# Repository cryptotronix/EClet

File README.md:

EClet
=====

Driver for the Cryptotronix EClet containing an Atmel ATECC108

Status
---

This software is in ***BETA***. I have tested the below commands, but some there are some features and documentation that I would like to finish. If you use this software, it will configure your ECC108 in a non-reversible way. It will allow you to sign and verify with P256 keys but future features may be incompatible.

Releases
-----

You can download the latest release [here](https://github.com/cryptotronix/EClet/releases/download/0.1.1/eclet-0.1.1.tar.gz). You will also need [this](https://github.com/cryptotronix/libcrypti2c/releases/download/v0.2/libcryptoauth-0.2.tar.gz) release of libcryptoauth.

Building
----

Install build-essential, autotools-dev, automake, autoconf, libtool, libxml2-dev, check, texinfo, and libgcrypt (libgcrypt11-dev on Debian variants)

Run `./autogen.sh`. This will generate the required README file from README.md as well as installing the required ***BETA*** version of [libcryptoauth-0.2](https://github.com/cryptotronix/libcrypti2c) (`sudo` is used to install this library)

You can run `eclet` locally, or install it to the system by running `sudo make install`

Hardware
---

The Hardware folder has an example board layout. This software will also work on the [CryptoCape](https://www.sparkfun.com/products/12773).

Running
---

see `./eclet --help` for full details.  The default I2C bus is
`/dev/i2c-1` and this can be changed with the `-b` option.

Kernel option
---

If you build
[libcryptoauth](https://github.com/cryptotronix/libcrypti2c) with the
`-DUSE_KERNEL` flag and install the kernel module, this utility will
use that module if you pass in: `-b /dev/atsha0`.

Root
---

You'll need to run as root to access `/dev/i2c*` initially.  You can change this by adding your user to the `i2c` group with:

`sudo usermod -aG i2c user`

Or:

`sudo chmod o+rw /dev/i2c*`

Currently supported commands:

### state
```bash
eclet state
Factory
```

This is the first command you should run and verify it's in the Factory state.  This provides the assurance that the device has not been tampered during transit.

### personalize
```bash
eclet personalize
```

This is the second command you should run.  On success it will not output anything. It configures all slots (0-16) to be holders for P-256 ECC private keys, except slot 8, which is reserved for future use. Keys are not generated at this time. Each key must be individually generated with the `gen-key` command.

***WARNING***

Until you personalize your device, the random number generator will produce a fixed test patterns of FFs and 00s. This is by design. However, it can be a bit suprising to see if you aren't expecting it.

### random
```bash
eclet random
62F95589AC76855A8F9204C9C6B8B85F06E6477D17C3888266AEE8E1CBD65319
```
### serial-num
```bash
eclet serial-num
0123XXXXXXXXXXXXEE
```
X's indicate the unique serial number.

### gen-key
```bash
eclet gen-key
04EED1CB629CF87F8BF6419986F990B92EA3DFA14CDAF70EB3E8DA8F9C9504DBC5B040D6480E88F895E9E1D4477970329B060450C80E1816EFED7B0FA49868CAEB
```

The device will internally create an P-256 ECC key and return the public key. The format of the public key is 0x04 + X + Y. Specify which slot to create a key (0-7, 9-15) with the `-k` option. Currently running this command multiple times will overwrite the public key, see this [issue](https://github.com/cryptotronix/EClet/issues/1).

### sign
```bash
eclet sign -f ChangeLog
3BAEB5705D8765B34B389F1768BAC783FCA786AB64A760D10DD133C86E5892A7A790E424C8E1540551C99FBE4F9F531B504A6004F08F3E0D4E42E96BBDE5C179
```

Performs an ECDSA signature. Data can be specified as a file with the `-f` option or passed via `stdin`. The data will be SHA256 hashed prior to signing. The result is the signature in the format: R + S.

### verify
```bash
eclet verify -f ChangeLog --signature C650D1A30194AD68F60F40C321FB084F6177BEDAC74D0F0C276ED35B00249AC8CF3E96FB7AB14AA48223FBA2E5DD9BCAE232BF963755C42F8FD9BD77FC145D41 --public-key 049B4A517704E16F3C99C6973E29F882EAF840DCD125C725C9552148A74349EB77BECB37AA2DB8056BAF0E236F6DCFEC2C5A9A0F23CEFD8A9DC1F4693718E725D2
```

Verifies an ECDSA signature using the device. You specify the data (which will be SHA256 hashed), the signature (R+S), and the public key (0x04+X+Y). Returns a `0` exit code on success.

### offline-verify-sign
```bash
eclet offline-verify-sign -f ChangeLog --signature C650D1A30194AD68F60F40C321FB084F6177BEDAC74D0F0C276ED35B00249AC8CF3E96FB7AB14AA48223FBA2E5DD9BCAE232BF963755C42F8FD9BD77FC145D41 --public-key 049B4A517704E16F3C99C6973E29F882EAF840DCD125C725C9552148A74349EB77BECB37AA2DB8056BAF0E236F6DCFEC2C5A9A0F23CEFD8A9DC1F4693718E725D2
```

Same as `verify` except it *does not* use the device and can be run on a system with one. It uses the software ECDSA implementation provided by `libcrypti2c`.

Options
---

Options are listed in the `--help` command, but a useful one, if there are issues, is the `-v` option.  This will dump all the data that travels across the I2C bus with the device.

Support
---

IRC: Join the `#cryptotronix` channel on freenode.

Mailing lists: `hashlet-announce` and `hashlet-users` are open for subscriptions [here](https://savannah.nongnu.org/mail/?group=hashlet).

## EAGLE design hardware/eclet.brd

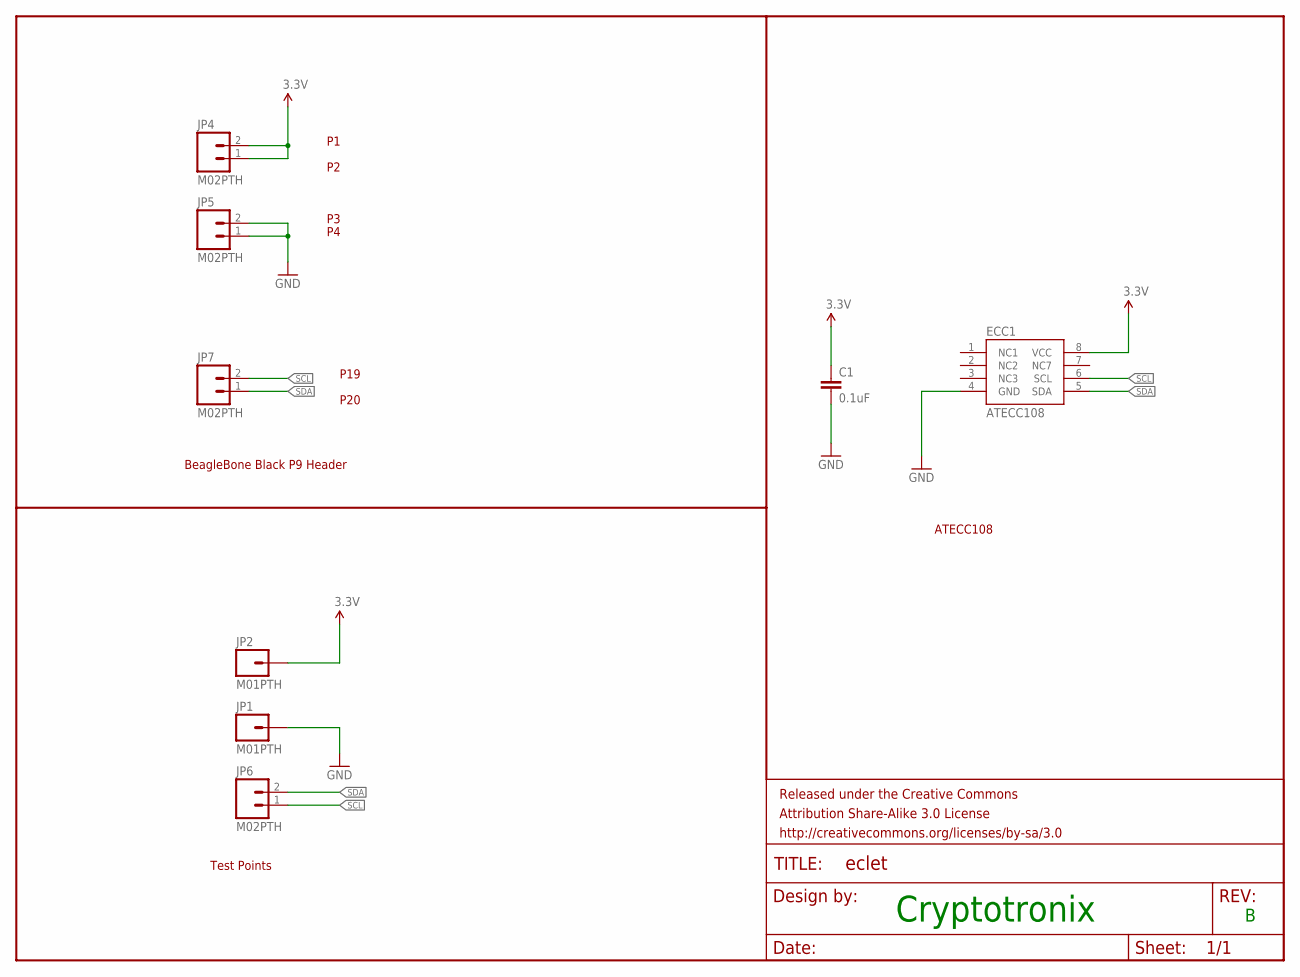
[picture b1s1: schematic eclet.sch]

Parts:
C1: 0.1uF; 0603-CAP
ECC1: ATECC108; SOIC8
FRAME1: FRAME-LETTER; CREATIVE_COMMONS
JP1, JP2: M01PTH; 1X01
JP4, JP5, JP6, JP7: M02PTH; 1X02

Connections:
3.3V: C1.1, ECC1.8 (VCC), JP2.1, JP4.1, JP4.2
GND: C1.2, ECC1.4 (GND), JP1.1, JP5.1, JP5.2
SCL: ECC1.6 (SCL), JP6.1, JP7.2
SDA: ECC1.5 (SDA), JP6.2, JP7.1

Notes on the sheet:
Cryptotronix
BeagleBone Black P9 Header
Test Points
P19
P20
ATECC108

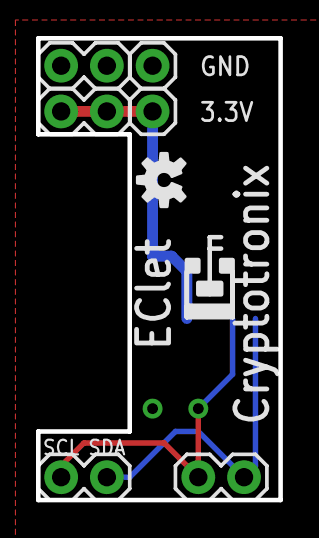
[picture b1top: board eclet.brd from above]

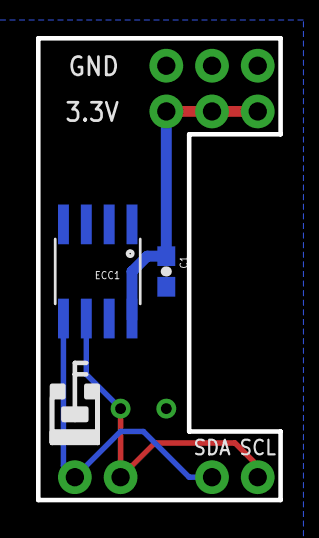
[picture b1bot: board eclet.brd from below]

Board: 2 copper layers, 13.5 x 25.7 mm, 10 parts (2 on the bottom side), 4 nets.

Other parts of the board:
U$1: OSHW-LOGO-S

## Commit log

2014-04-03 adds autotools setup
2014-04-03 Adds source
2014-05-23 Interm commit.
2014-05-24 Refactored to use new library interface.
2014-05-24 Adds initial doc structure.
2014-05-25 Removed unused commands.
2014-05-25 Sign and verify appear to be working.
2014-05-25 Moves hash functions to libcrypti2c.
2014-05-25 Removes depends on libgcrypt.
2014-05-25 Removes hashlet code.
2014-05-25 Adds file for travis.ci
2014-05-25 Updates autogen for travis
2014-05-25 Removes custom install script.
2014-05-25 Adds missing depends from travis install
2014-05-25 Adds travis status
2014-05-25 Adds tests for offline verify sign.
2014-05-25 offline verify works.
2014-05-25 Cleans up log comments.
2014-05-25 Fixes pub_key to always return back with the uncompressed point tag.
    - Every time pub_key is returned it should start with 0x04.
    - Online verifies must scrub the 0x04 before sending it to the device.
2014-05-25 Cleanup on documentation.
    Adds sudo ldconfig to autogen.
2014-05-25 Cleans up cli commands.
2014-05-25 Cleans up command files
2014-05-25 Additional code cleanup.
2014-05-26 Updates README.
2014-05-27 Adds factory test script.
2014-05-27 Adds hardware design files
2014-05-27 Adds temporary fix for issue #4.
2014-09-08 Updates code for new library ABI.
2014-09-08 Updates to guile-2.0
2014-09-08 Adds specific checkout command to get the testing branch.
2014-09-08 Adds missing function prototype.
2014-09-09 Adds data zone parameter to write 32.
2014-11-03 Tested with kernel driver.
2015-03-23 Adds warning on README
    Adds warning on README to indicate that the RNG will exhibit the test pattern until personalized.
2015-04-08 refactors to use libcryptoauth vs libcrypti2c
2015-04-08 Adds compile flag for kernel use.
2015-04-08 Updates autogen script to use new library.
2015-04-08 Fixes travis build, hopefully.
2015-04-08 Adds depends to travis.yml
2015-04-08 Removes compile switches as libcryptoauth will abstract this.
2015-04-08 Adds check depends
2015-04-08 Bumps required library version.
2015-04-08 Updates for new library version.
2015-04-08 fixes autogen script.
2015-04-09 Adds break statement (coverity catch)
2015-04-09 Fixes coverity error.
2015-04-09 really fixes coverity error.
2015-04-09 Updates readme
2015-04-09 Version 0.1 was short lived.
2015-04-09 Updates README
    Includes links to the released software.
2015-12-08 General build cleanups
2015-12-08 General build cleanups and doc updates
2015-12-08 More readme updates
2016-08-15 It's compiling with latest libraries.

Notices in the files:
README.md:
GPLv3
parts and their libraries:
SparkFun-Connectors: Licensing: CC v3.0 Share-Alike You are welcome to use this library for commercial purposes.
SparkFun-Aesthetics: Released under the Creative Commons Attribution Share-Alike 3.0 License
SparkFun-Aesthetics: http://creativecommons.org/licenses/by-sa/3.0
